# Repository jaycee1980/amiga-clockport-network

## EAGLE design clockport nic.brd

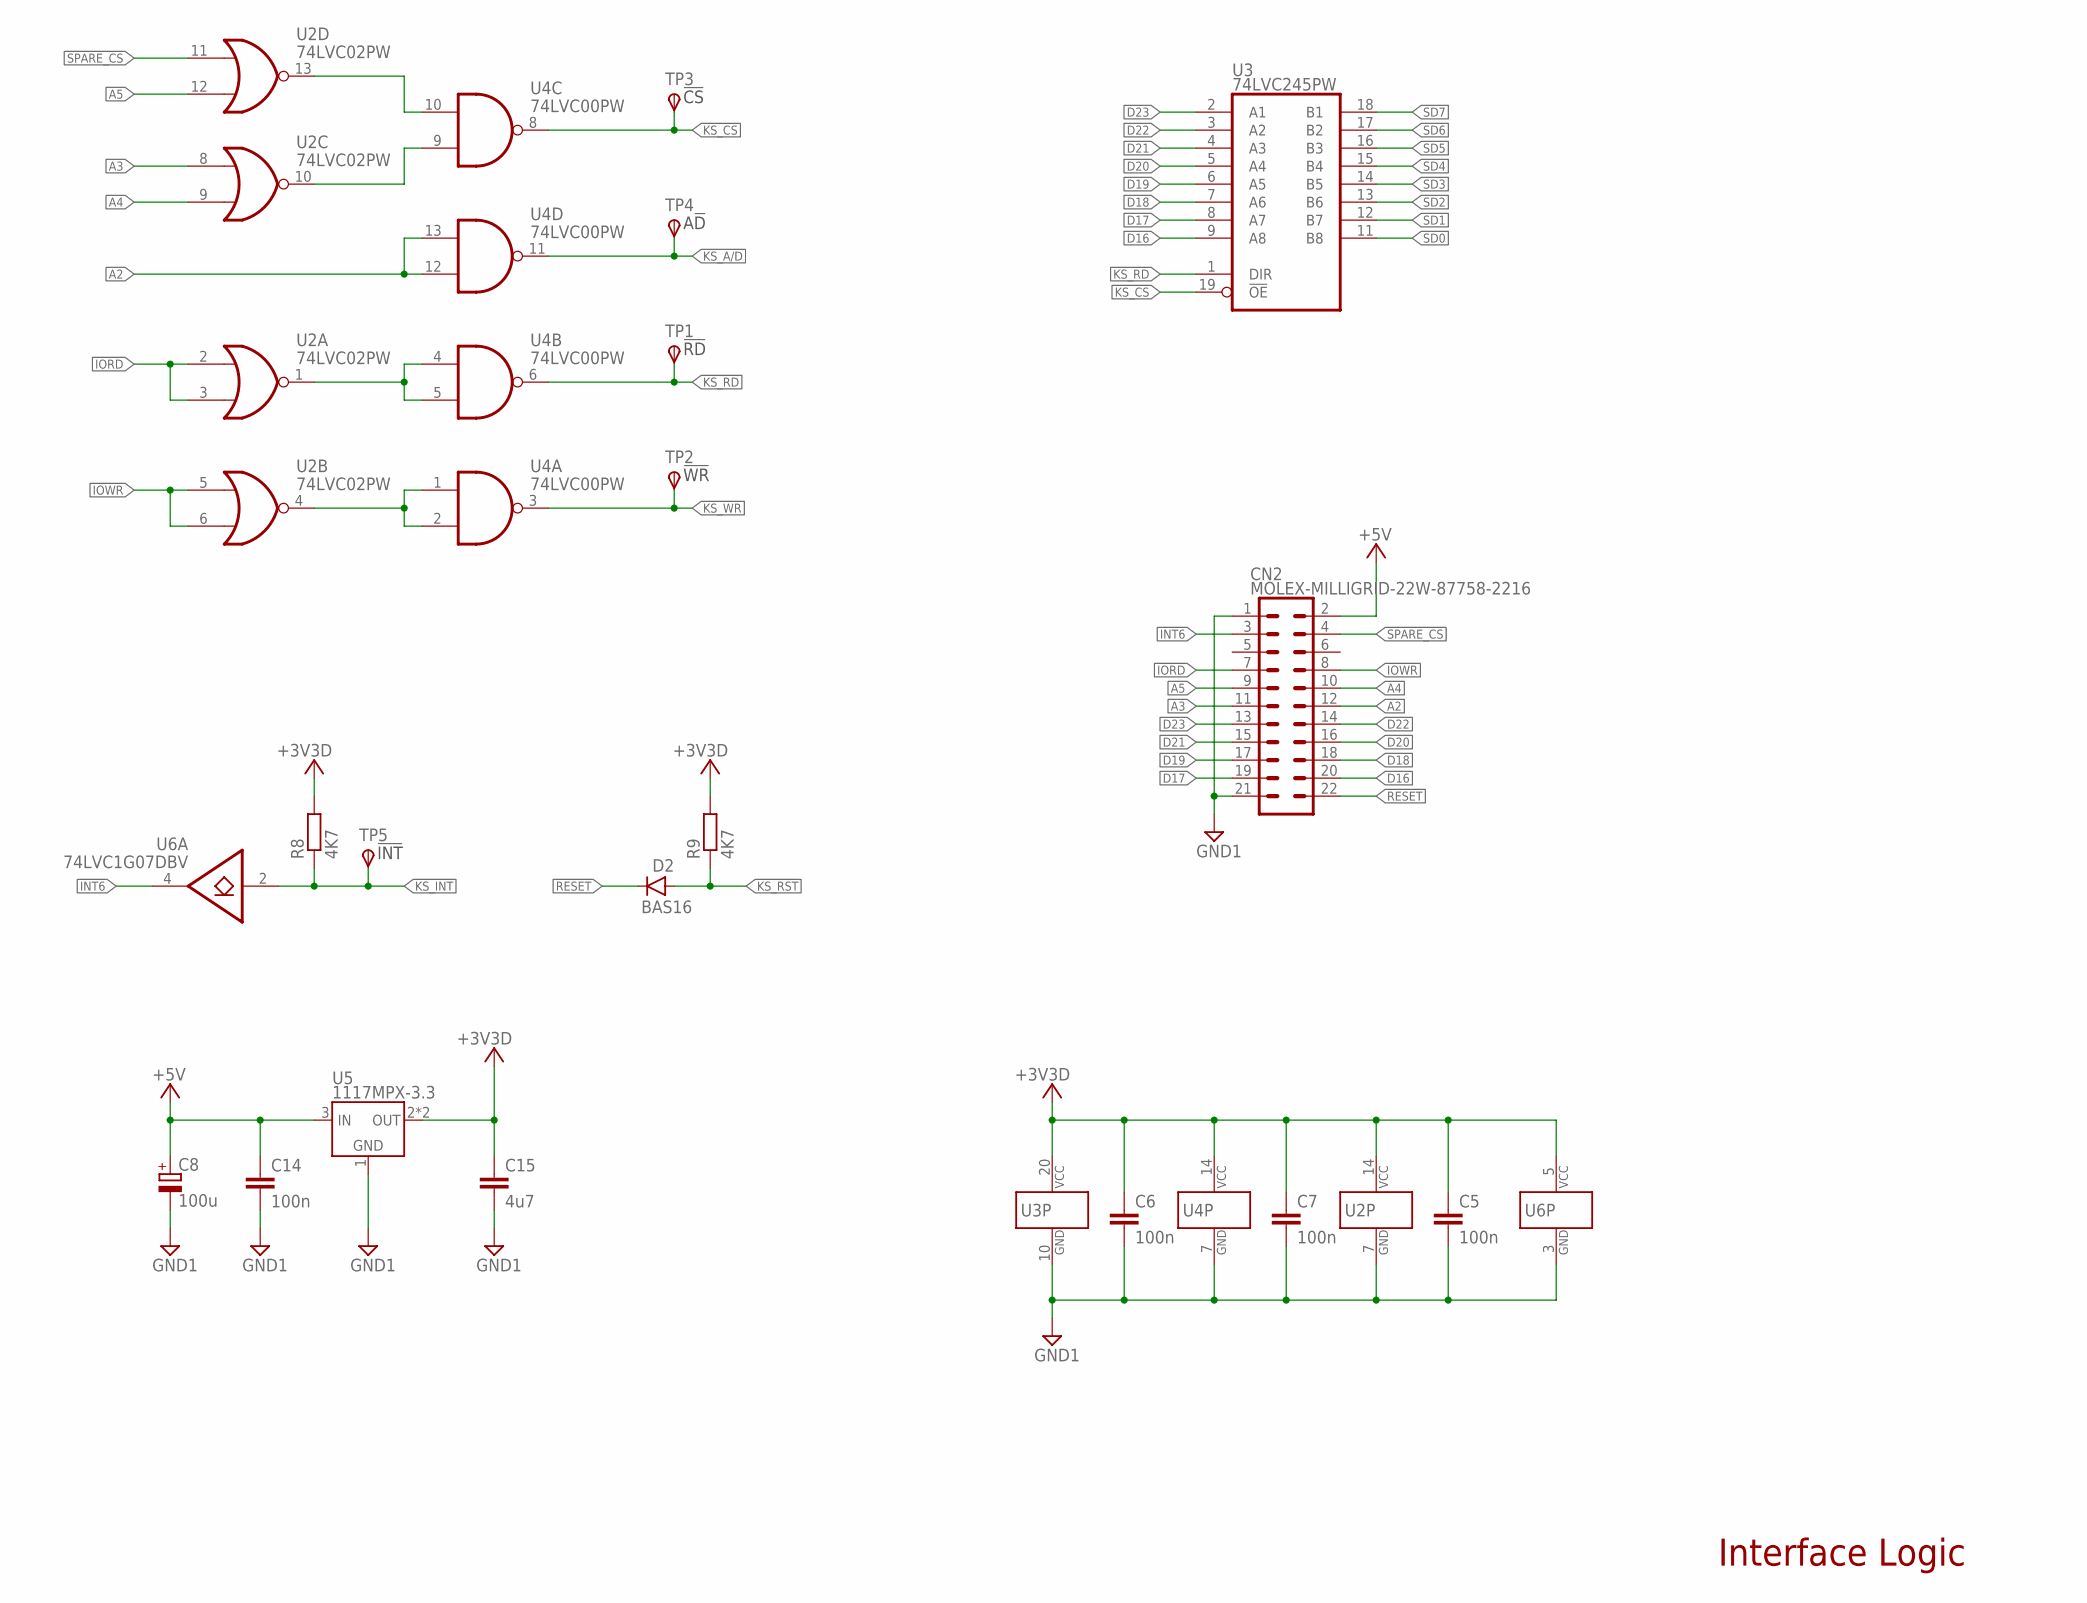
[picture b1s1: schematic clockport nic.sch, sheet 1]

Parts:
C5, C6, C7, C14: 100n; C0603
C8: 100u; E2,5-6
C15: 4u7; C0805
CN2: MOLEX-MILLIGRID-22W-87758-2216; MOLEX-87758-2216
D2: BAS16; SOD323-R
R8, R9: 4K7; R0603
TP1, TP2, TP3, TP4, TP5: TPSB1,27; B1,27
U2: 74LVC02PW; TSSOP14
U3: 74LVC245PW; TSSOP20
U4: 74LVC00PW; TSSOP14
U5: 1117MPX-3.3; SOT223
U6: 74LVC1G07DBV; SOT23-5

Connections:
!INT6: CN2.3, U6.4 (O)
!IORD: CN2.7, U2.2 (I0), U2.3 (I1)
!IOWR: CN2.8, U2.5 (I0), U2.6 (I1)
!KS_CS: TP3.TP, U3.19 (!OE), U4.8 (O); also elsewhere on the board
!KS_INT: R8.1, TP5.TP, U6.2 (I); also elsewhere on the board
!KS_RD: TP1.TP, U3.1 (DIR), U4.6 (O); also elsewhere on the board
!KS_RST: D2.A, R9.1; also elsewhere on the board
!KS_WR: TP2.TP, U4.3 (O); also elsewhere on the board
!RESET: CN2.22, D2.K (C)
!SPARE_CS: CN2.4, U2.11 (I0)
+3V3D: C5.1, C6.1, C7.1, C15.1, R8.2, R9.2, U2.14 (VCC), U3.20 (VCC), U4.14 (VCC), U5.2 (OUT), U5.4 (OUT), U6.5 (VCC); also elsewhere on the board
+5V: C8.+, C14.1, CN2.2, U5.3 (IN)
A2: CN2.12, U4.12 (I1), U4.13 (I0)
A3: CN2.11, U2.8 (I0)
A4: CN2.10, U2.9 (I1)
A5: CN2.9, U2.12 (I1)
D16: CN2.20, U3.9 (A8)
D17: CN2.19, U3.8 (A7)
D18: CN2.18, U3.7 (A6)
D19: CN2.17, U3.6 (A5)
D20: CN2.16, U3.5 (A4)
D21: CN2.15, U3.4 (A3)
D22: CN2.14, U3.3 (A2)
D23: CN2.13, U3.2 (A1)
GND1: C5.2, C6.2, C7.2, C8.-, C14.2, C15.2, CN2.1, CN2.21, U2.7 (GND), U3.10 (GND), U4.7 (GND), U5.1 (GND), U6.3 (GND); also elsewhere on the board
KS_A/!D: TP4.TP, U4.11 (O); also elsewhere on the board
unnamed: U2.4 (O), U4.1 (I0), U4.2 (I1)
unnamed: U2.1 (O), U4.4 (I0), U4.5 (I1)
unnamed: U2.10 (O), U4.9 (I1)
unnamed: U2.13 (O), U4.10 (I0)
SD0: U3.11 (B8); also elsewhere on the board
SD1: U3.12 (B7); also elsewhere on the board
SD2: U3.13 (B6); also elsewhere on the board
SD3: U3.14 (B5); also elsewhere on the board
SD4: U3.15 (B4); also elsewhere on the board
SD5: U3.16 (B3); also elsewhere on the board
SD6: U3.17 (B2); also elsewhere on the board
SD7: U3.18 (B1); also elsewhere on the board

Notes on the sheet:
Interface Logic

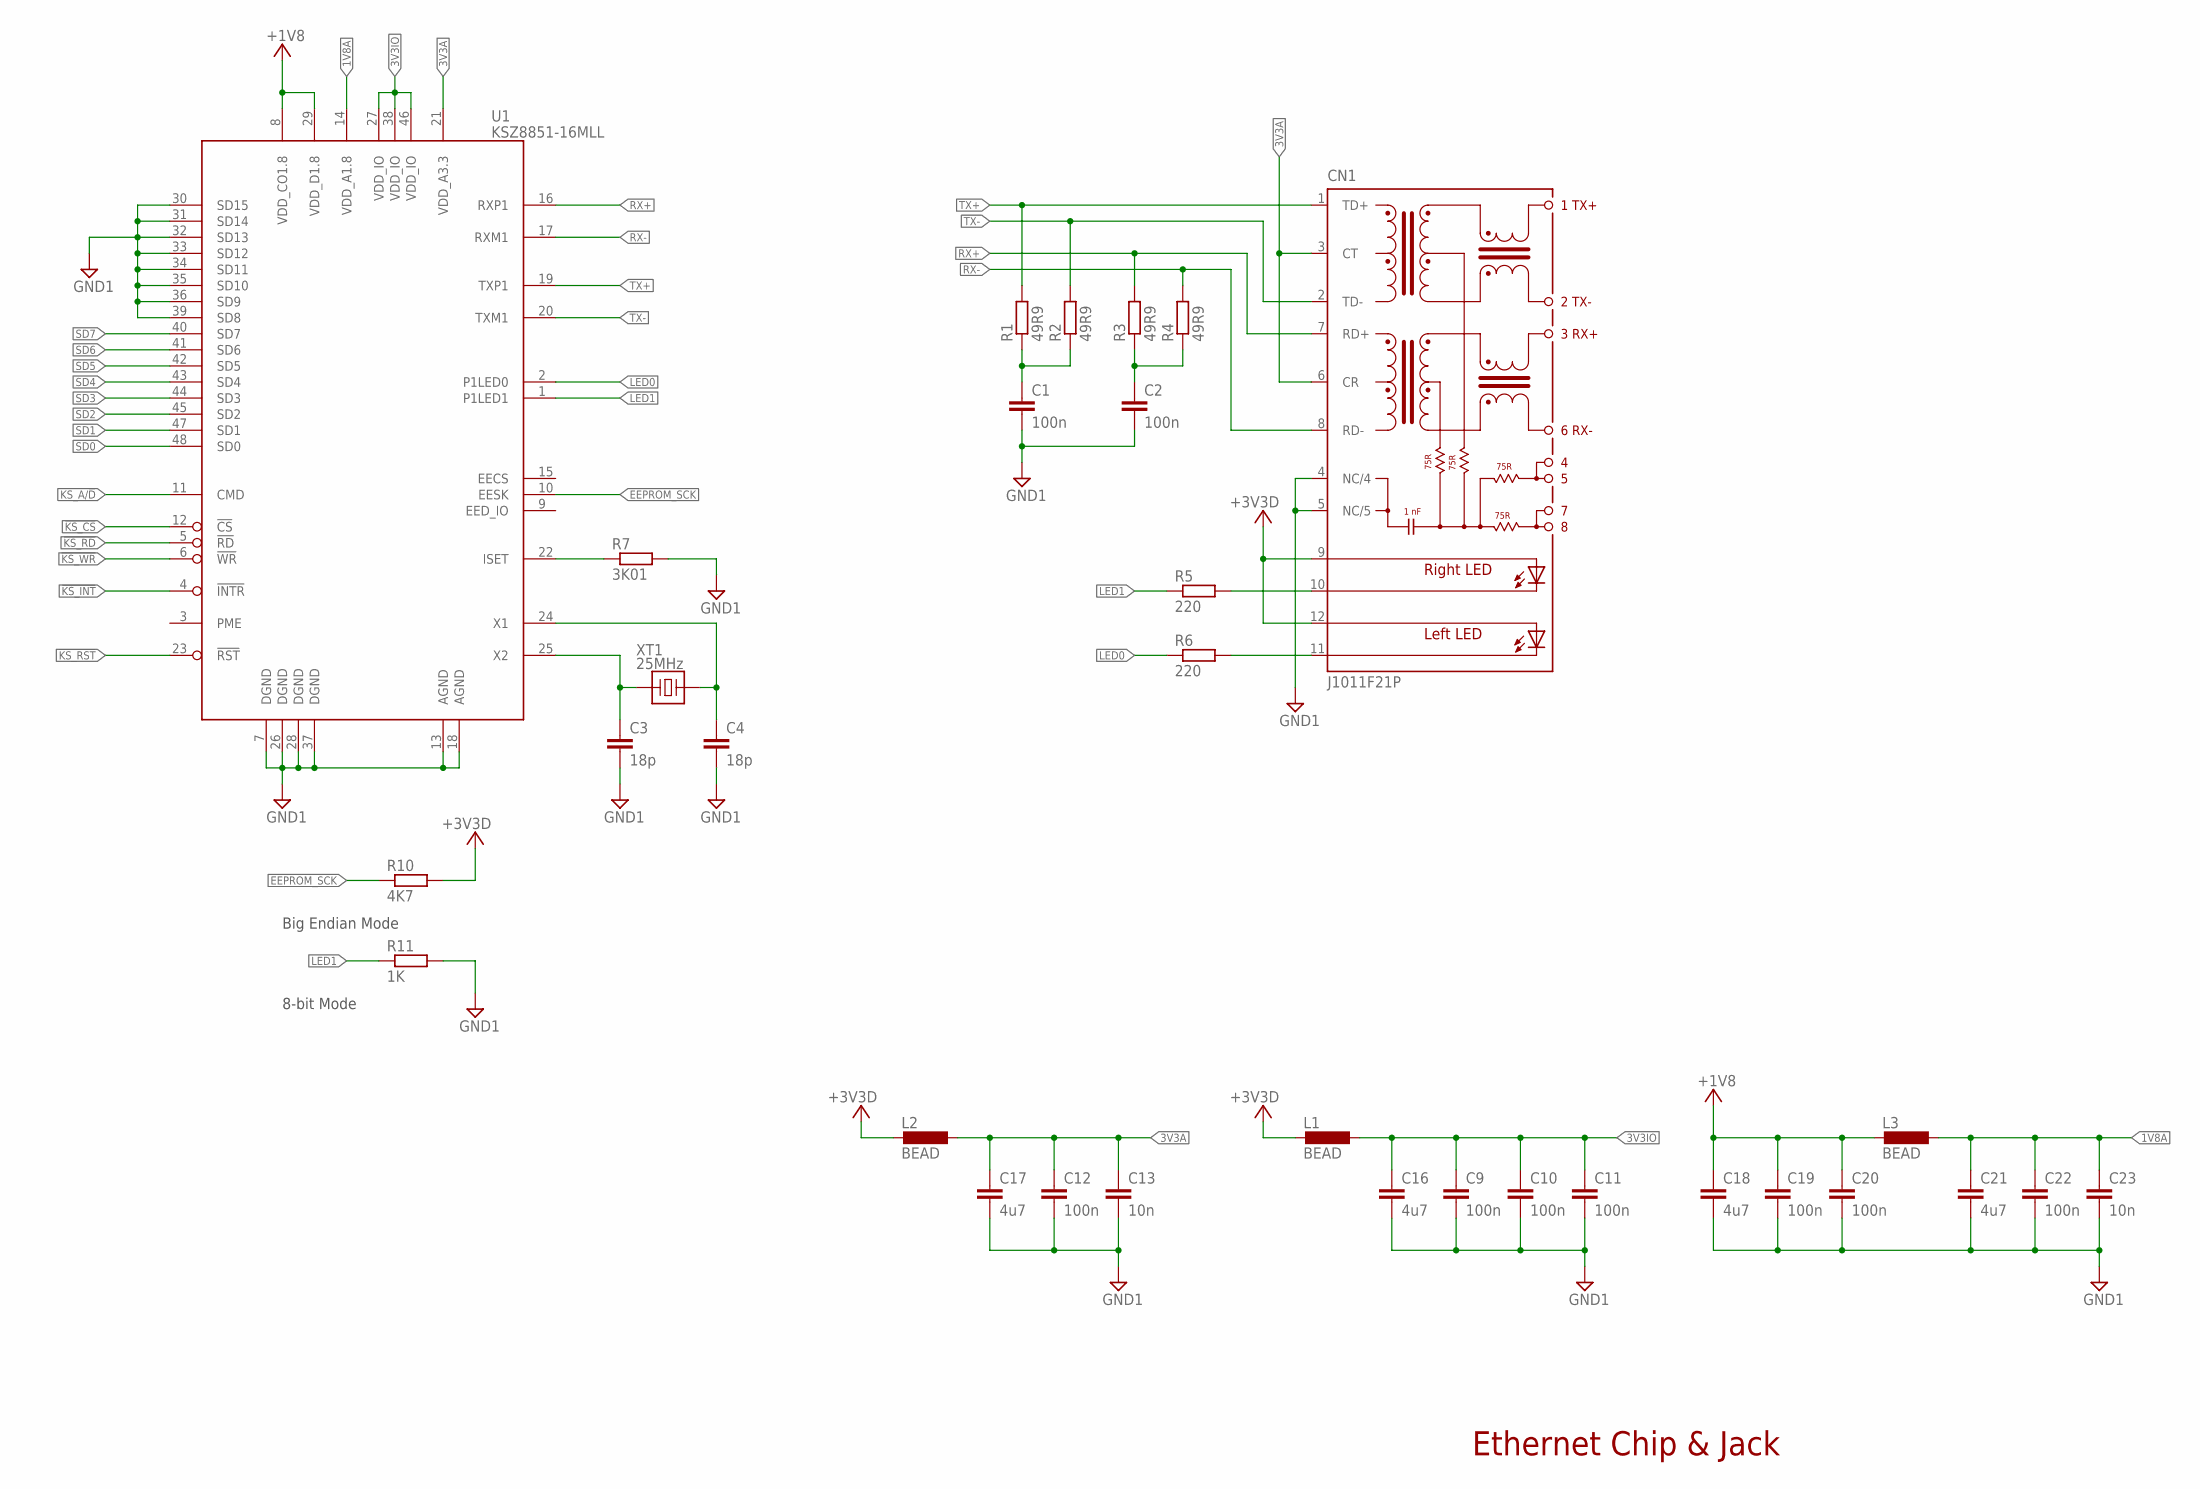
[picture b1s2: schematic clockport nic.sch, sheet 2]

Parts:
C1, C2, C9, C10, C11, C12, C19, C20, C22: 100n; C0603
C3, C4: 18p; C0603
C13, C23: 10n; C0603
C16, C17, C18, C21: 4u7; C0805
CN1: J1011F21P; J1
L1, L2, L3: BEAD; L2012C
R1, R2, R3, R4: 49R9; R0603
R5, R6: 220; R0603
R7: 3K01; R0603
R10: 4K7; R0603
R11: 1K; R0603
U1: KSZ8851-16MLL; LQFP48
XT1: 25MHz; 3225_4PAD

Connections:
1V8A: C21.1, C22.1, C23.1, L3.1, U1.14 (VDD_A1.8)
3V3A: C12.1, C13.1, C17.1, CN1.3 (CT), CN1.6 (CR), L2.1, U1.21 (VDD_A3.3)
3V3IO: C9.1, C10.1, C11.1, C16.1, L1.1, U1.27 (VDD_IO), U1.38 (VDD_IO), U1.46 (VDD_IO)
!KS_CS: U1.12 (!CS); also elsewhere on the board
!KS_INT: U1.4 (!INTR); also elsewhere on the board
!KS_RD: U1.5 (!RD); also elsewhere on the board
!KS_RST: U1.23 (!RST); also elsewhere on the board
!KS_WR: U1.6 (!WR); also elsewhere on the board
+1V8: C18.1, C19.1, C20.1, L3.2, U1.8 (VDD_CO1.8), U1.29 (VDD_D1.8)
+3V3D: CN1.9 (A-R), CN1.12 (AL), L1.2, L2.2, R10.2; also elsewhere on the board
EEPROM_SCK: R10.1, U1.10 (EESK)
GND1: C1.2, C2.2, C3.2, C4.2, C9.2, C10.2, C11.2, C12.2, C13.2, C16.2, C17.2, C18.2, C19.2, C20.2, C21.2, C22.2, C23.2, CN1.4 (NC/4), CN1.5 (NC/5), R7.2, R11.2, U1.7 (DGND), U1.13 (AGND), U1.18 (AGND), U1.26 (DGND), U1.28 (DGND), U1.30 (SD15), U1.31 (SD14), U1.32 (SD13), U1.33 (SD12), U1.34 (SD11), U1.35 (SD10), U1.36 (SD9), U1.37 (DGND), U1.39 (SD8); also elsewhere on the board
ISET: R7.1, U1.22 (ISET)
KS_A/!D: U1.11 (CMD); also elsewhere on the board
LED0: R6.1, U1.2 (P1LED0)
LED1: R5.1, R11.1, U1.1 (P1LED1)
unnamed: C2.1, R3.1, R4.1
unnamed: CN1.11 (C-L), R6.2
unnamed: CN1.10 (C-R), R5.2
unnamed: C1.1, R1.1, R2.1
RX+: CN1.7 (RD+), R3.2, U1.16 (RXP1)
RX-: CN1.8 (RD-), R4.2, U1.17 (RXM1)
SD0: U1.48 (SD0); also elsewhere on the board
SD1: U1.47 (SD1); also elsewhere on the board
SD2: U1.45 (SD2); also elsewhere on the board
SD3: U1.44 (SD3); also elsewhere on the board
SD4: U1.43 (SD4); also elsewhere on the board
SD5: U1.42 (SD5); also elsewhere on the board
SD6: U1.41 (SD6); also elsewhere on the board
SD7: U1.40 (SD7); also elsewhere on the board
TX+: CN1.1 (TD+), R1.2, U1.19 (TXP1)
TX-: CN1.2 (TD-), R2.2, U1.20 (TXM1)
XT1: C4.1, U1.24 (X1), XT1.3 (2)
XT2: C3.1, U1.25 (X2), XT1.1

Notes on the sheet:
Ethernet Chip & Jack
Big Endian Mode
8-bit Mode

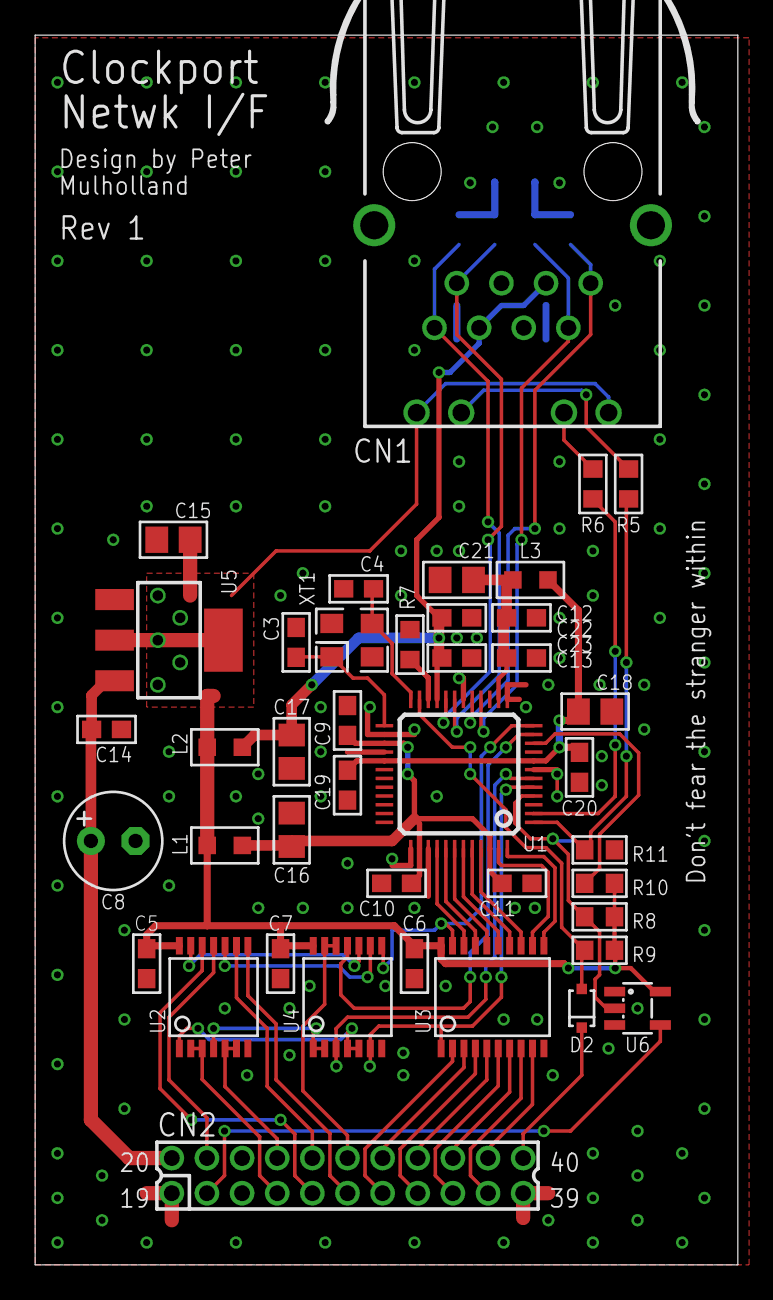
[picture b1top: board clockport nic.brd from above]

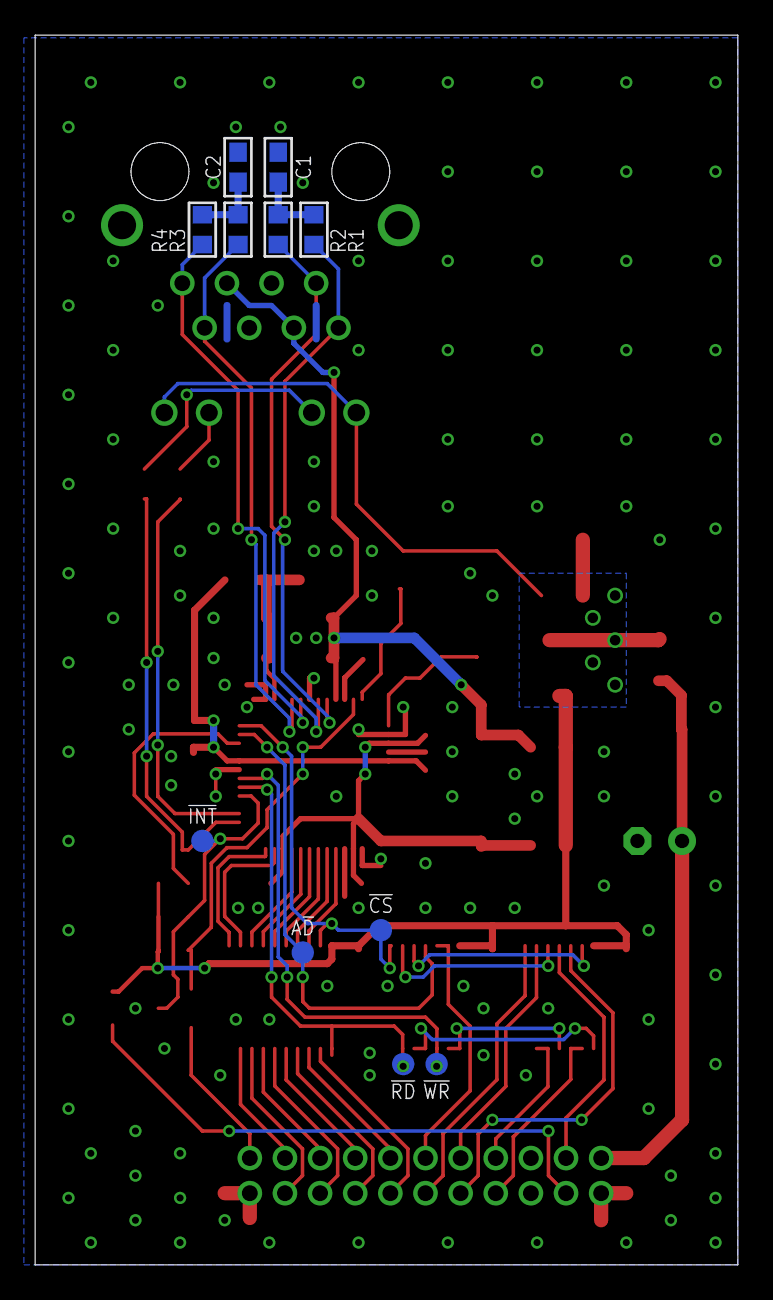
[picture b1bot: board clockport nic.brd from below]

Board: 2 copper layers, 40.0 x 70.0 mm, 52 parts (11 on the bottom side), 56 nets.
